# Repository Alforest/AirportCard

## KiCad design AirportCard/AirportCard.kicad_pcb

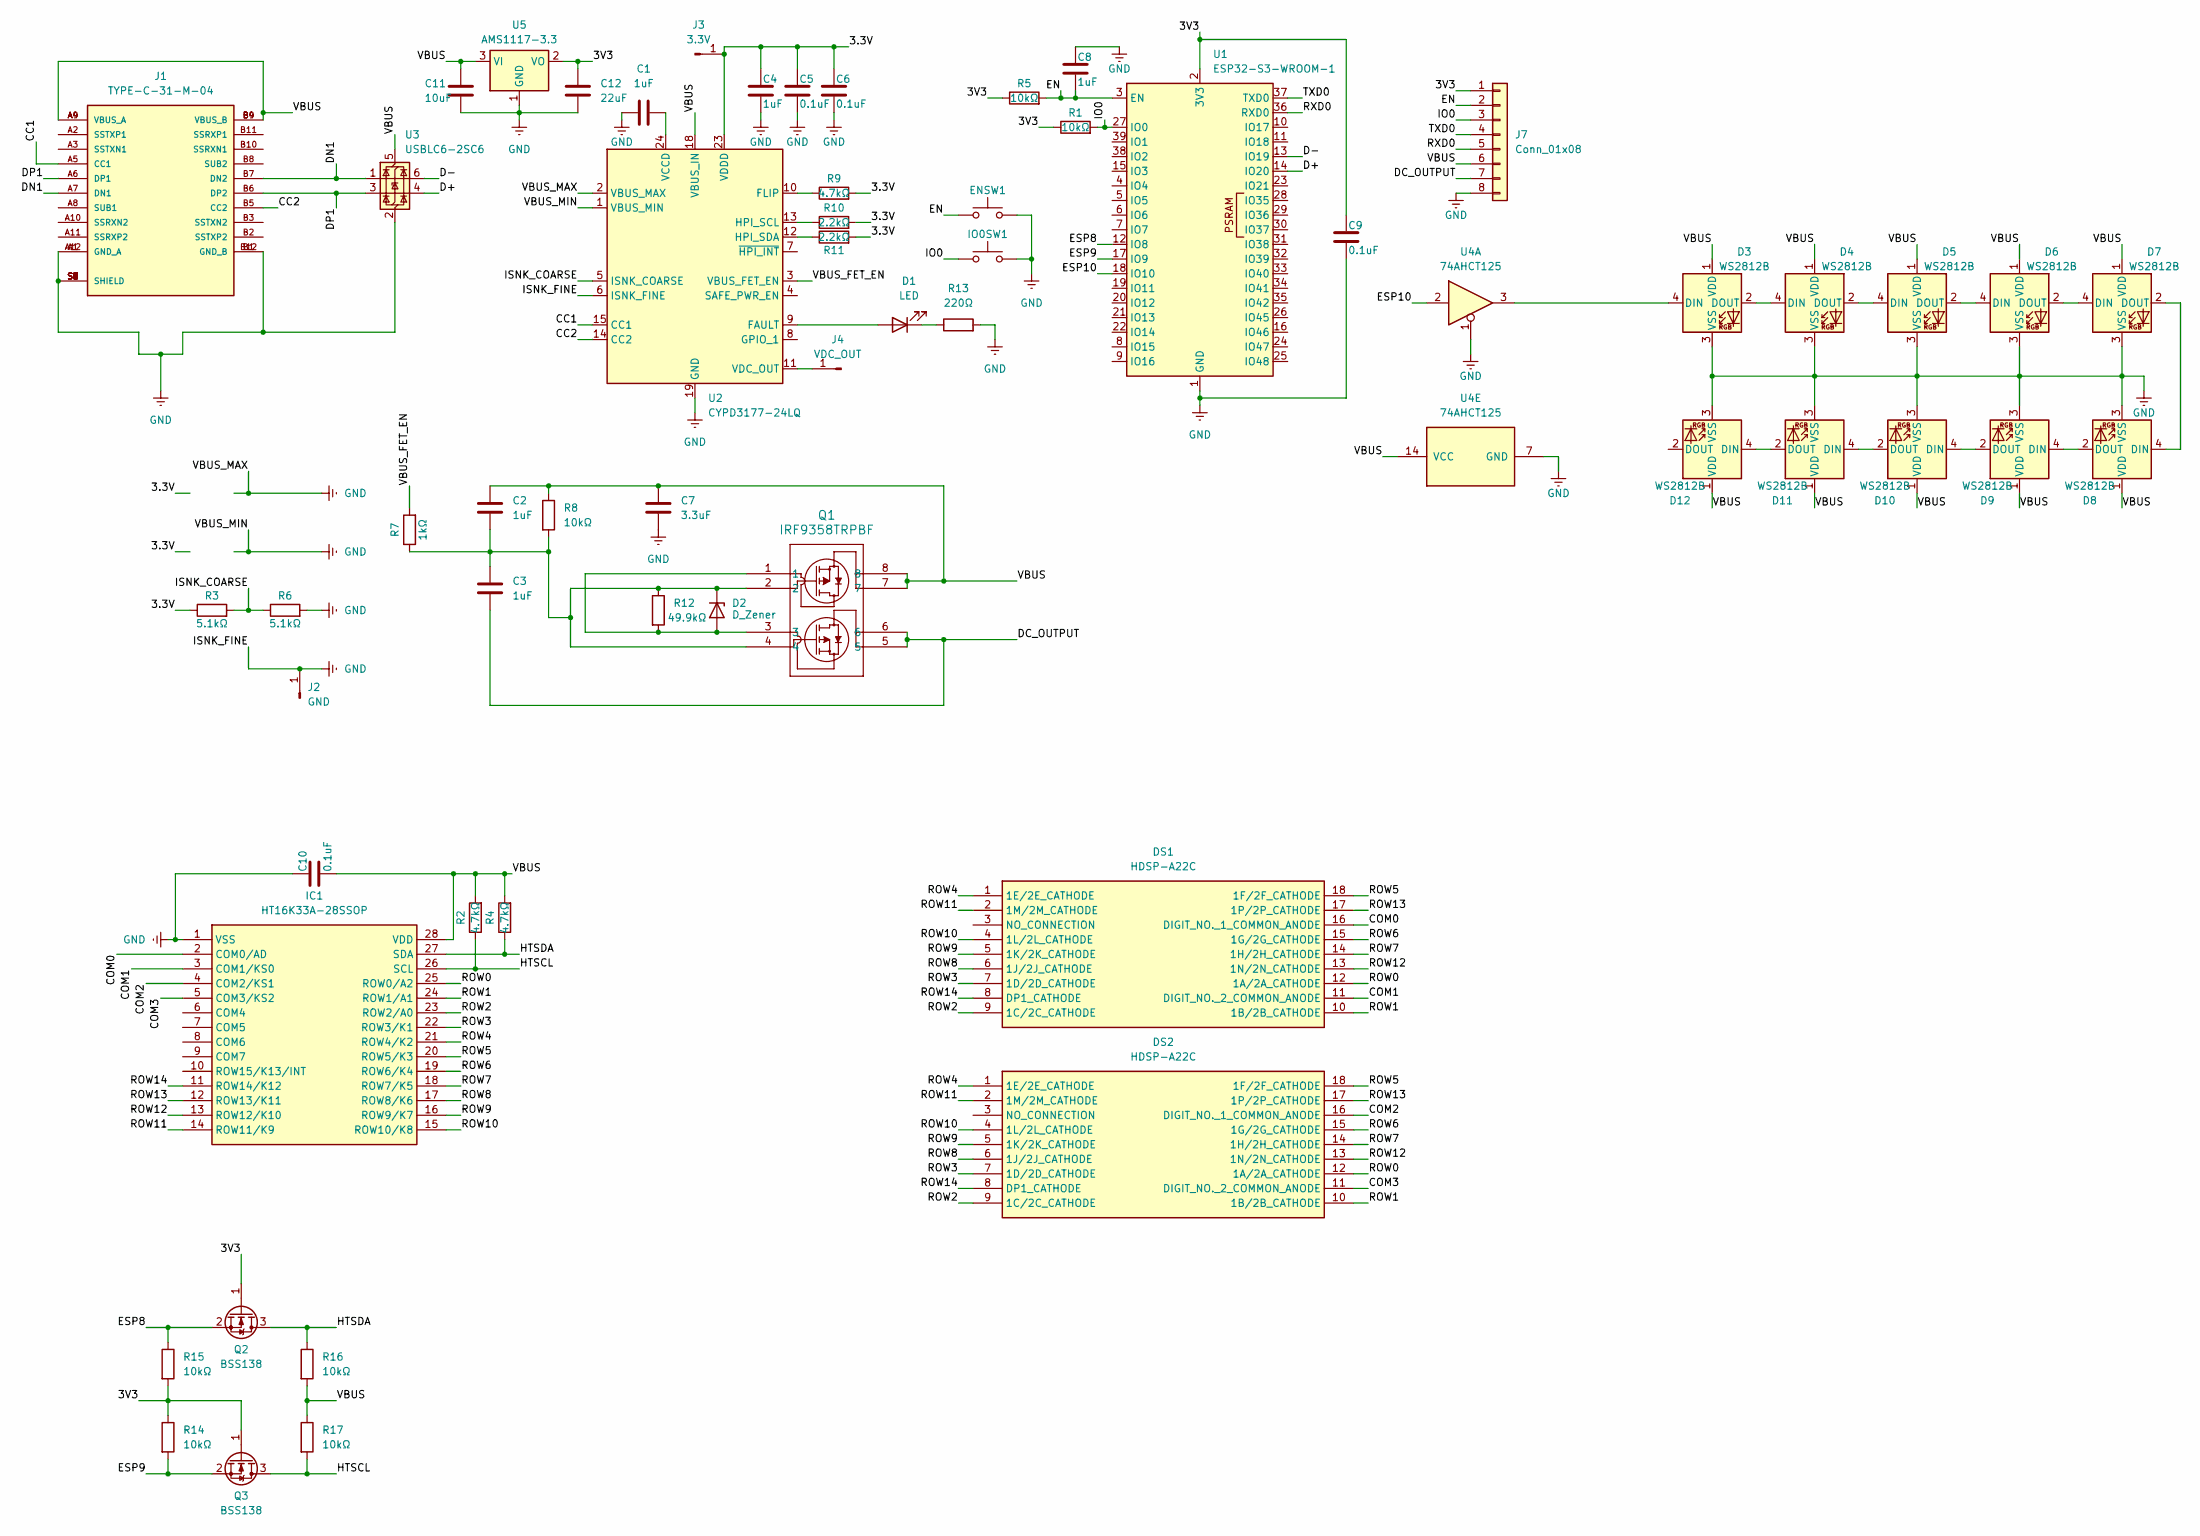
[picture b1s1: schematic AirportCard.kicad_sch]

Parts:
C1, C2, C3, C4, C8: 1uF; C_0603_1608Metric_Pad1.08x0.95mm_HandSolder
C5, C6, C9, C10: 0.1uF; C_0603_1608Metric_Pad1.08x0.95mm_HandSolder
C7: 3.3uF; C_0603_1608Metric_Pad1.08x0.95mm_HandSolder
C11: 10uF; C_0603_1608Metric_Pad1.08x0.95mm_HandSolder
C12: 22uF; C_0603_1608Metric_Pad1.08x0.95mm_HandSolder
D1: LED; LED_0603_1608Metric_Pad1.05x0.95mm_HandSolder
D2: D_Zener; D_SOD-123F
D3, D4, D5, D6, D7, D8, D9, D10, D11, D12: WS2812B; LED_WS2812B_PLCC4_5.0x5.0mm_P3.2mm
DS1, DS2: HDSP-A22C; DIPS1524W51P254L2520H725Q18N; Manufacturer_Part_Number HDSP-A22C; Mouser Part Number 630-HDSP-A22C
ENSW1: SW_Push; SW_PUSH_6mm
IC1: HT16K33A-28SSOP; SOP64P600X175-28N; Manufacturer_Part_Number HT16K33A-28SSOP
IO0SW1: SW_Push; SW_PUSH_6mm
J1: TYPE-C-31-M-04; HRO_TYPE-C-31-M-04; PARTREV A
J2: GND; PinHeader_1x01_P2.54mm_Vertical
J3: 3.3V; PinHeader_1x01_P2.54mm_Vertical
J4: VDC_OUT; PinHeader_1x01_P2.54mm_Vertical
J7: Conn_01x08; PinHeader_1x08_P2.00mm_Horizontal
Q1: IRF9358TRPBF; SO-8_3.9x4.9mm_P1.27mm
Q2, Q3: BSS138; SOT-23
R1, R5, R8, R14, R15, R16, R17: 10kΩ; R_0603_1608Metric_Pad0.98x0.95mm_HandSolder
R2, R4: 4.7kΩ; R_Axial_DIN0207_L6.3mm_D2.5mm_P7.62mm_Horizontal
R3, R6: 5.1kΩ; R_0603_1608Metric_Pad0.98x0.95mm_HandSolder
R7: 1kΩ; R_0603_1608Metric_Pad0.98x0.95mm_HandSolder
R9: 4.7kΩ; R_0603_1608Metric_Pad0.98x0.95mm_HandSolder
R10, R11: 2.2kΩ; R_0603_1608Metric_Pad0.98x0.95mm_HandSolder
R12: 49.9kΩ; R_0603_1608Metric_Pad0.98x0.95mm_HandSolder
R13: 220Ω; R_0603_1608Metric_Pad0.98x0.95mm_HandSolder
U1: ESP32-S3-WROOM-1
U2: CYPD3177-24LQ; QFN-24-1EP_4x4mm_P0.5mm_EP2.75x2.75mm
U3: USBLC6-2SC6; SOT-23-6
U4: 74AHCT125; SOP65P640X120-14N
U5: AMS1117-3.3; SOT-223-3_TabPin2

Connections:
/3.3V: C4.1, C5.1, C6.1, J3.1, R3.1, R9.2, R10.2, R11.2, U2.23 (VDDD)
/3V3: C9.1, C12.1, J7.1, Q2.1 (G), Q3.1 (G), R1.1, R5.1, R14.1, R15.2, U1.2 (3V3), U5.2 (VO)
/CC1: J1.A5 (CC1), U2.15 (CC1)
/CC2: J1.B5 (CC2), U2.14 (CC2)
/COM0: DS1.16 (DIGIT_NO._1_COMMON_ANODE), IC1.2 (COM0/AD)
/COM1: DS1.11 (DIGIT_NO._2_COMMON_ANODE), IC1.3 (COM1/KS0)
/COM2: DS2.16 (DIGIT_NO._1_COMMON_ANODE), IC1.4 (COM2/KS1)
/COM3: DS2.11 (DIGIT_NO._2_COMMON_ANODE), IC1.5 (COM3/KS2)
/D+: U1.14 (IO20), U3.4 (I/O2)
/D-: U1.13 (IO19), U3.6 (I/O1)
/DC_OUTPUT: C3.2, J7.7, Q1.5, Q1.6
/DN1: J1.A7 (DN1), J1.B7 (DN2), U3.1 (I/O1)
/DP1: J1.A6 (DP1), J1.B6 (DP2), U3.3 (I/O2)
/EN: C8.2, ENSW1.1, J7.2, R5.2, U1.3 (EN)
/ESP8: Q2.2 (S), R15.1, U1.12 (IO8)
/ESP9: Q3.2 (S), R14.2, U1.17 (IO9)
/ESP10: U1.18 (IO10), U4.2
/HTSCL: IC1.26 (SCL), Q3.3 (D), R2.1, R17.2
/HTSDA: IC1.27 (SDA), Q2.3 (D), R4.1, R16.1
/IO0: IO0SW1.1, J7.3, R1.2, U1.27 (IO0)
/ISNK_COARSE: R3.2, R6.1, U2.5 (ISNK_COARSE)
/ROW0: DS1.12 (1A/2A_CATHODE), DS2.12 (1A/2A_CATHODE), IC1.25 (ROW0/A2)
/ROW1: DS1.10 (1B/2B_CATHODE), DS2.10 (1B/2B_CATHODE), IC1.24 (ROW1/A1)
/ROW2: DS1.9 (1C/2C_CATHODE), DS2.9 (1C/2C_CATHODE), IC1.23 (ROW2/A0)
/ROW3: DS1.7 (1D/2D_CATHODE), DS2.7 (1D/2D_CATHODE), IC1.22 (ROW3/K1)
/ROW4: DS1.1 (1E/2E_CATHODE), DS2.1 (1E/2E_CATHODE), IC1.21 (ROW4/K2)
/ROW5: DS1.18 (1F/2F_CATHODE), DS2.18 (1F/2F_CATHODE), IC1.20 (ROW5/K3)
/ROW6: DS1.15 (1G/2G_CATHODE), DS2.15 (1G/2G_CATHODE), IC1.19 (ROW6/K4)
/ROW7: DS1.14 (1H/2H_CATHODE), DS2.14 (1H/2H_CATHODE), IC1.18 (ROW7/K5)
/ROW8: DS1.6 (1J/2J_CATHODE), DS2.6 (1J/2J_CATHODE), IC1.17 (ROW8/K6)
/ROW9: DS1.5 (1K/2K_CATHODE), DS2.5 (1K/2K_CATHODE), IC1.16 (ROW9/K7)
/ROW10: DS1.4 (1L/2L_CATHODE), DS2.4 (1L/2L_CATHODE), IC1.15 (ROW10/K8)
/ROW11: DS1.2 (1M/2M_CATHODE), DS2.2 (1M/2M_CATHODE), IC1.14 (ROW11/K9)
/ROW12: DS1.13 (1N/2N_CATHODE), DS2.13 (1N/2N_CATHODE), IC1.13 (ROW12/K10)
/ROW13: DS1.17 (1P/2P_CATHODE), DS2.17 (1P/2P_CATHODE), IC1.12 (ROW13/K11)
/ROW14: DS1.8 (DP1_CATHODE), DS2.8 (DP1_CATHODE), IC1.11 (ROW14/K12)
/RXD0: J7.5, U1.36 (RXD0)
/TXD0: J7.4, U1.37 (TXD0)
/VBUS: C2.1, C7.1, C10.2, C11.1, D3.1 (VDD), D4.1 (VDD), D5.1 (VDD), D6.1 (VDD), D7.1 (VDD), D8.1 (VDD), D9.1 (VDD), D10.1 (VDD), D11.1 (VDD), D12.1 (VDD), IC1.28 (VDD), J1.A4 (VBUS_A), J1.A9 (VBUS_A), J1.B4 (VBUS_B), J1.B9 (VBUS_B), J7.6, Q1.7, Q1.8, R2.2, R4.2, R8.1, R16.2, R17.1, U2.18 (VBUS_IN), U3.5 (VBUS), U4.14 (VCC), U5.3 (VI)
/VBUS_FET_EN: R7.2, U2.3 (VBUS_FET_EN)
GND: C1.1, C4.2, C5.2, C6.2, C7.2, C8.1, C9.2, C10.1, C11.2, C12.2, D3.3 (VSS), D4.3 (VSS), D5.3 (VSS), D6.3 (VSS), D7.3 (VSS), D8.3 (VSS), D9.3 (VSS), D10.3 (VSS), D11.3 (VSS), D12.3 (VSS), ENSW1.2, IC1.1 (VSS), IO0SW1.2, J1.A1 (GND_A), J1.A12 (GND_A), J1.B1 (GND_B), J1.B12 (GND_B), J1.S1 (SHIELD), J1.S2 (SHIELD), J1.S3 (SHIELD), J1.S4 (SHIELD), J1.S5 (SHIELD), J1.S6 (SHIELD), J1.S7 (SHIELD), J1.S8 (SHIELD), J2.1, J7.8, R6.2, R13.2, U1.1 (GND), U1.40 (GND), U1.41 (GND), U2.1 (VBUS_MIN), U2.2 (VBUS_MAX), U2.6 (ISNK_FINE), U2.19 (GND), U2.22 (GND), U2.25 (GND), U3.2 (GND), U4.1, U4.7 (GND), U5.1 (GND)
unnamed: D1.2 (A), U2.9 (FAULT)
unnamed: D1.1 (K), R13.1
unnamed: D2.2 (A), Q1.1, Q1.3, R12.2
unnamed: C2.2, C3.1, D2.1 (K), Q1.2, Q1.4, R7.1, R8.2, R12.1
unnamed: D3.4 (DIN), U4.3
unnamed: D3.2 (DOUT), D4.4 (DIN)
unnamed: D4.2 (DOUT), D5.4 (DIN)
unnamed: D5.2 (DOUT), D6.4 (DIN)
unnamed: D6.2 (DOUT), D7.4 (DIN)
unnamed: D7.2 (DOUT), D8.4 (DIN)
unnamed: D8.2 (DOUT), D9.4 (DIN)
unnamed: D9.2 (DOUT), D10.4 (DIN)
unnamed: D10.2 (DOUT), D11.4 (DIN)
unnamed: D11.2 (DOUT), D12.4 (DIN)
unnamed: J4.1, U2.11 (VDC_OUT)
unnamed: R9.1, U2.10 (FLIP)
unnamed: R10.1, U2.13 (HPI_SCL)
unnamed: R11.1, U2.12 (HPI_SDA)
unnamed: C1.2, U2.24 (VCCD)

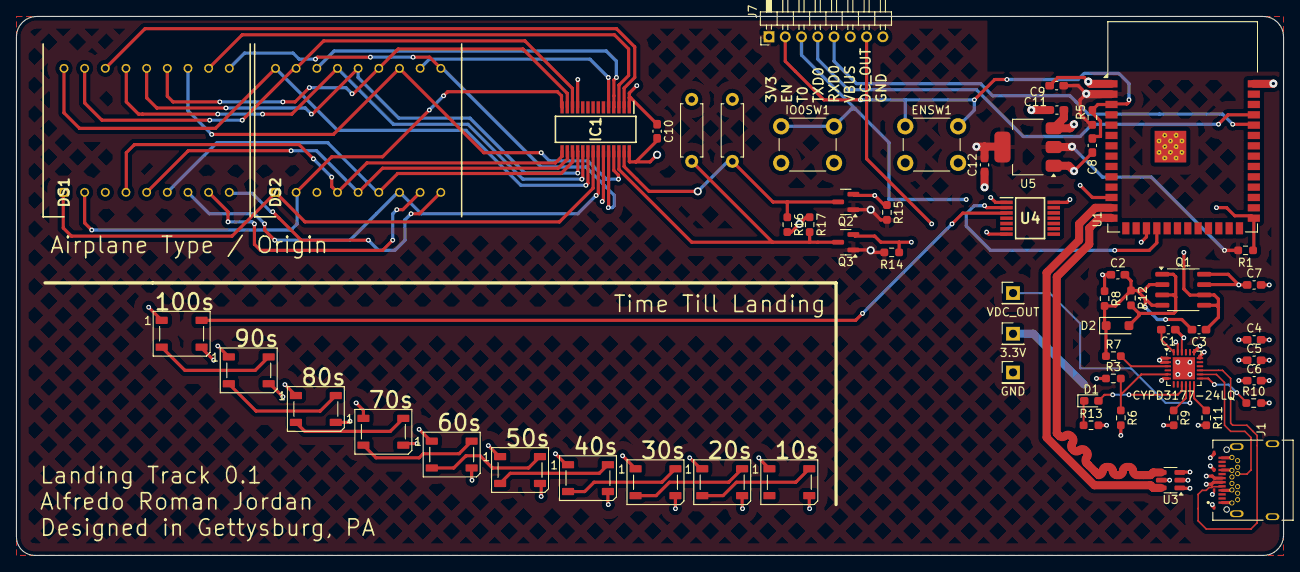
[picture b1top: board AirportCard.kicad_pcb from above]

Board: 4 copper layers, 155.8 x 66.2 mm, 59 parts (0 on the bottom side), 60 nets.
